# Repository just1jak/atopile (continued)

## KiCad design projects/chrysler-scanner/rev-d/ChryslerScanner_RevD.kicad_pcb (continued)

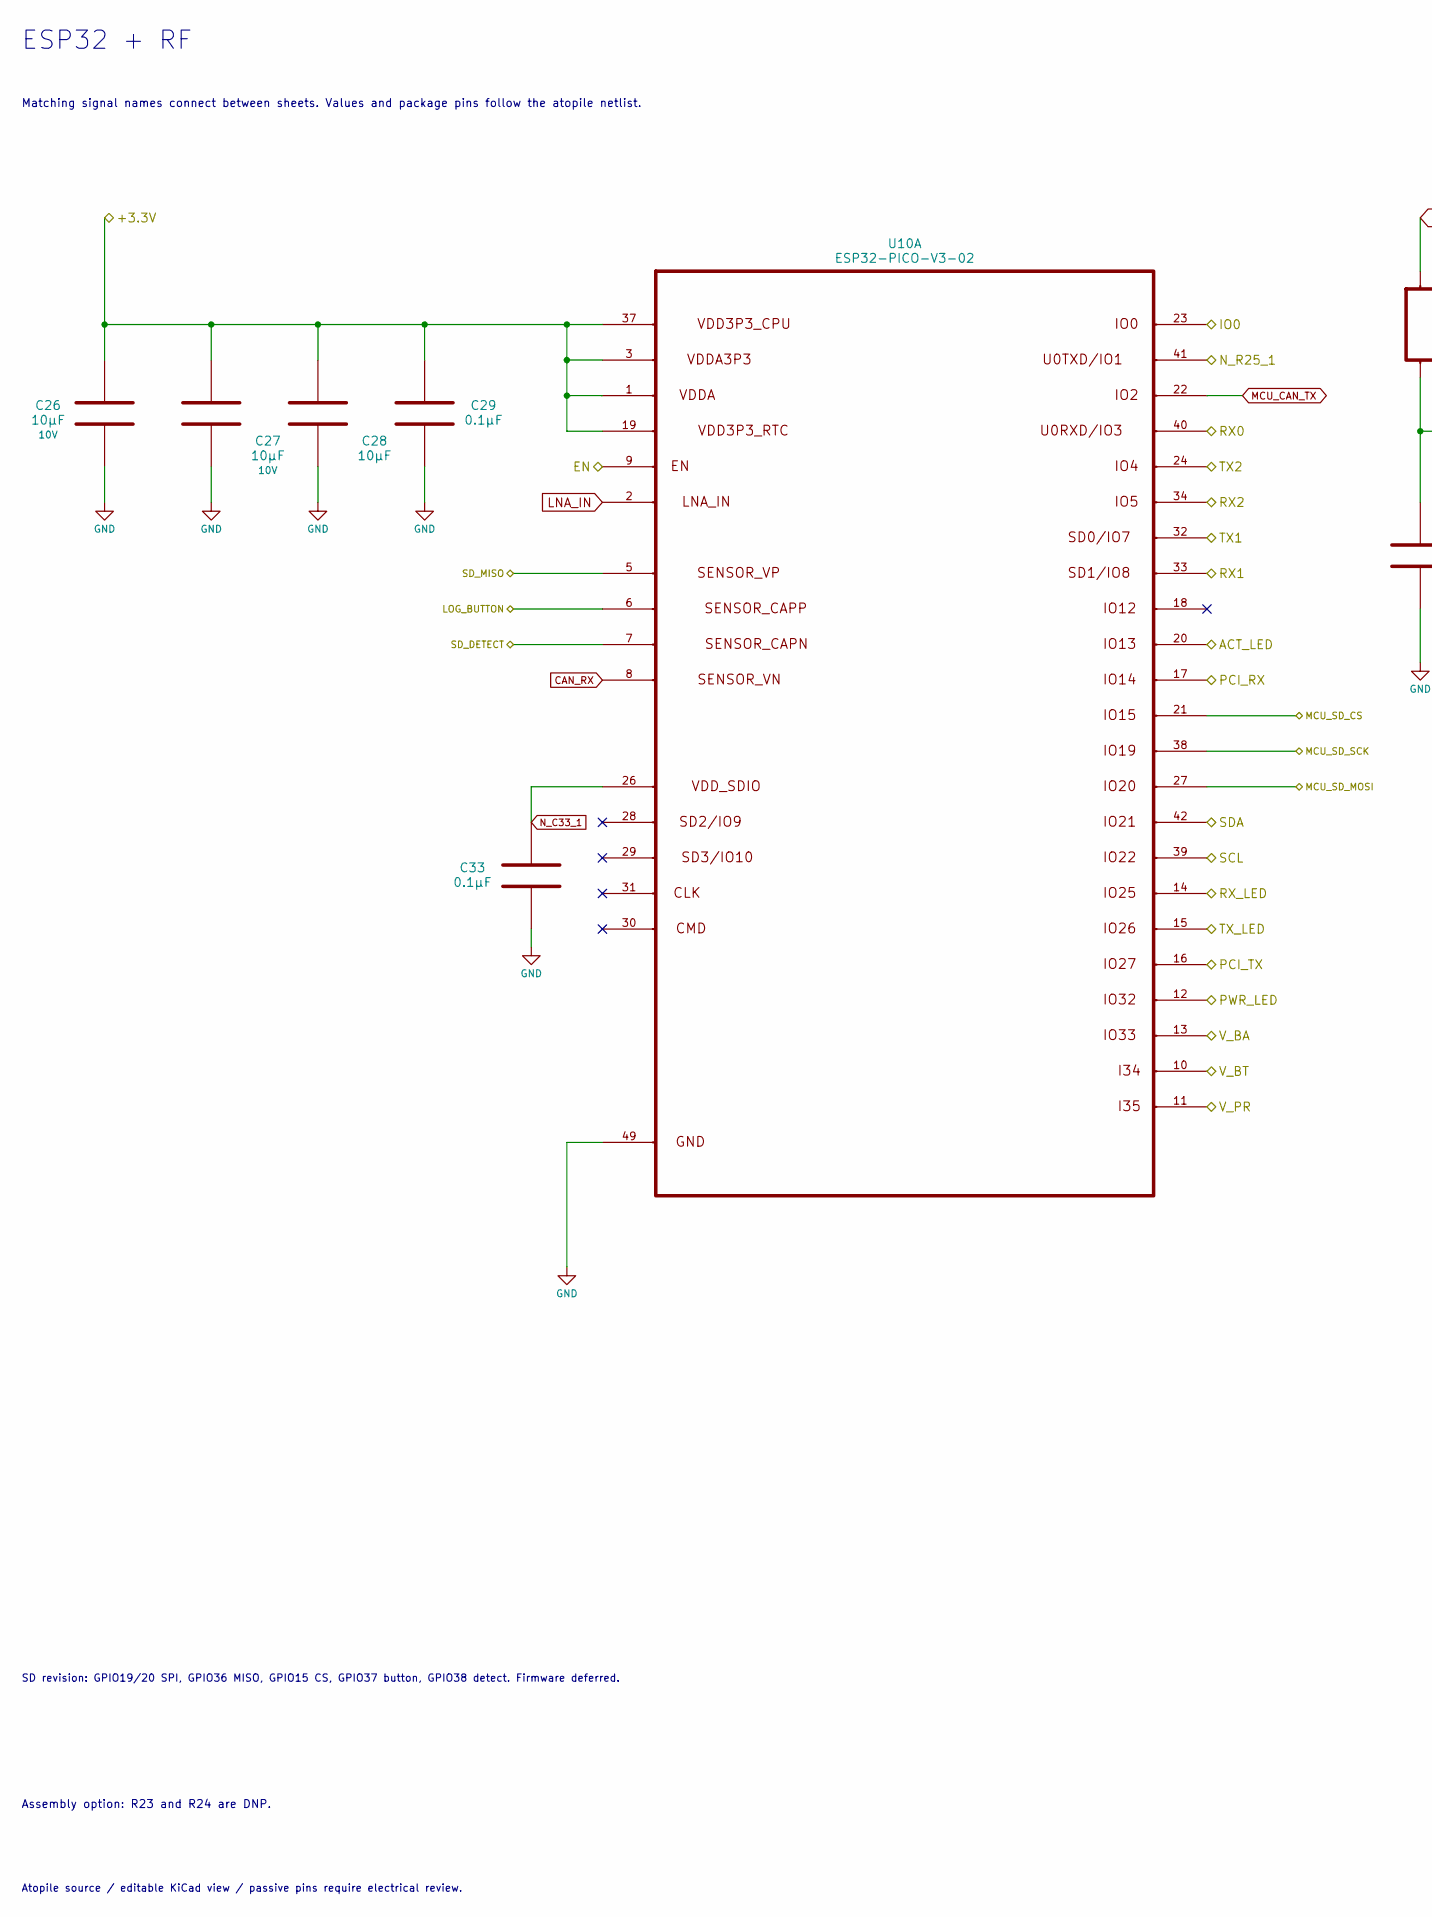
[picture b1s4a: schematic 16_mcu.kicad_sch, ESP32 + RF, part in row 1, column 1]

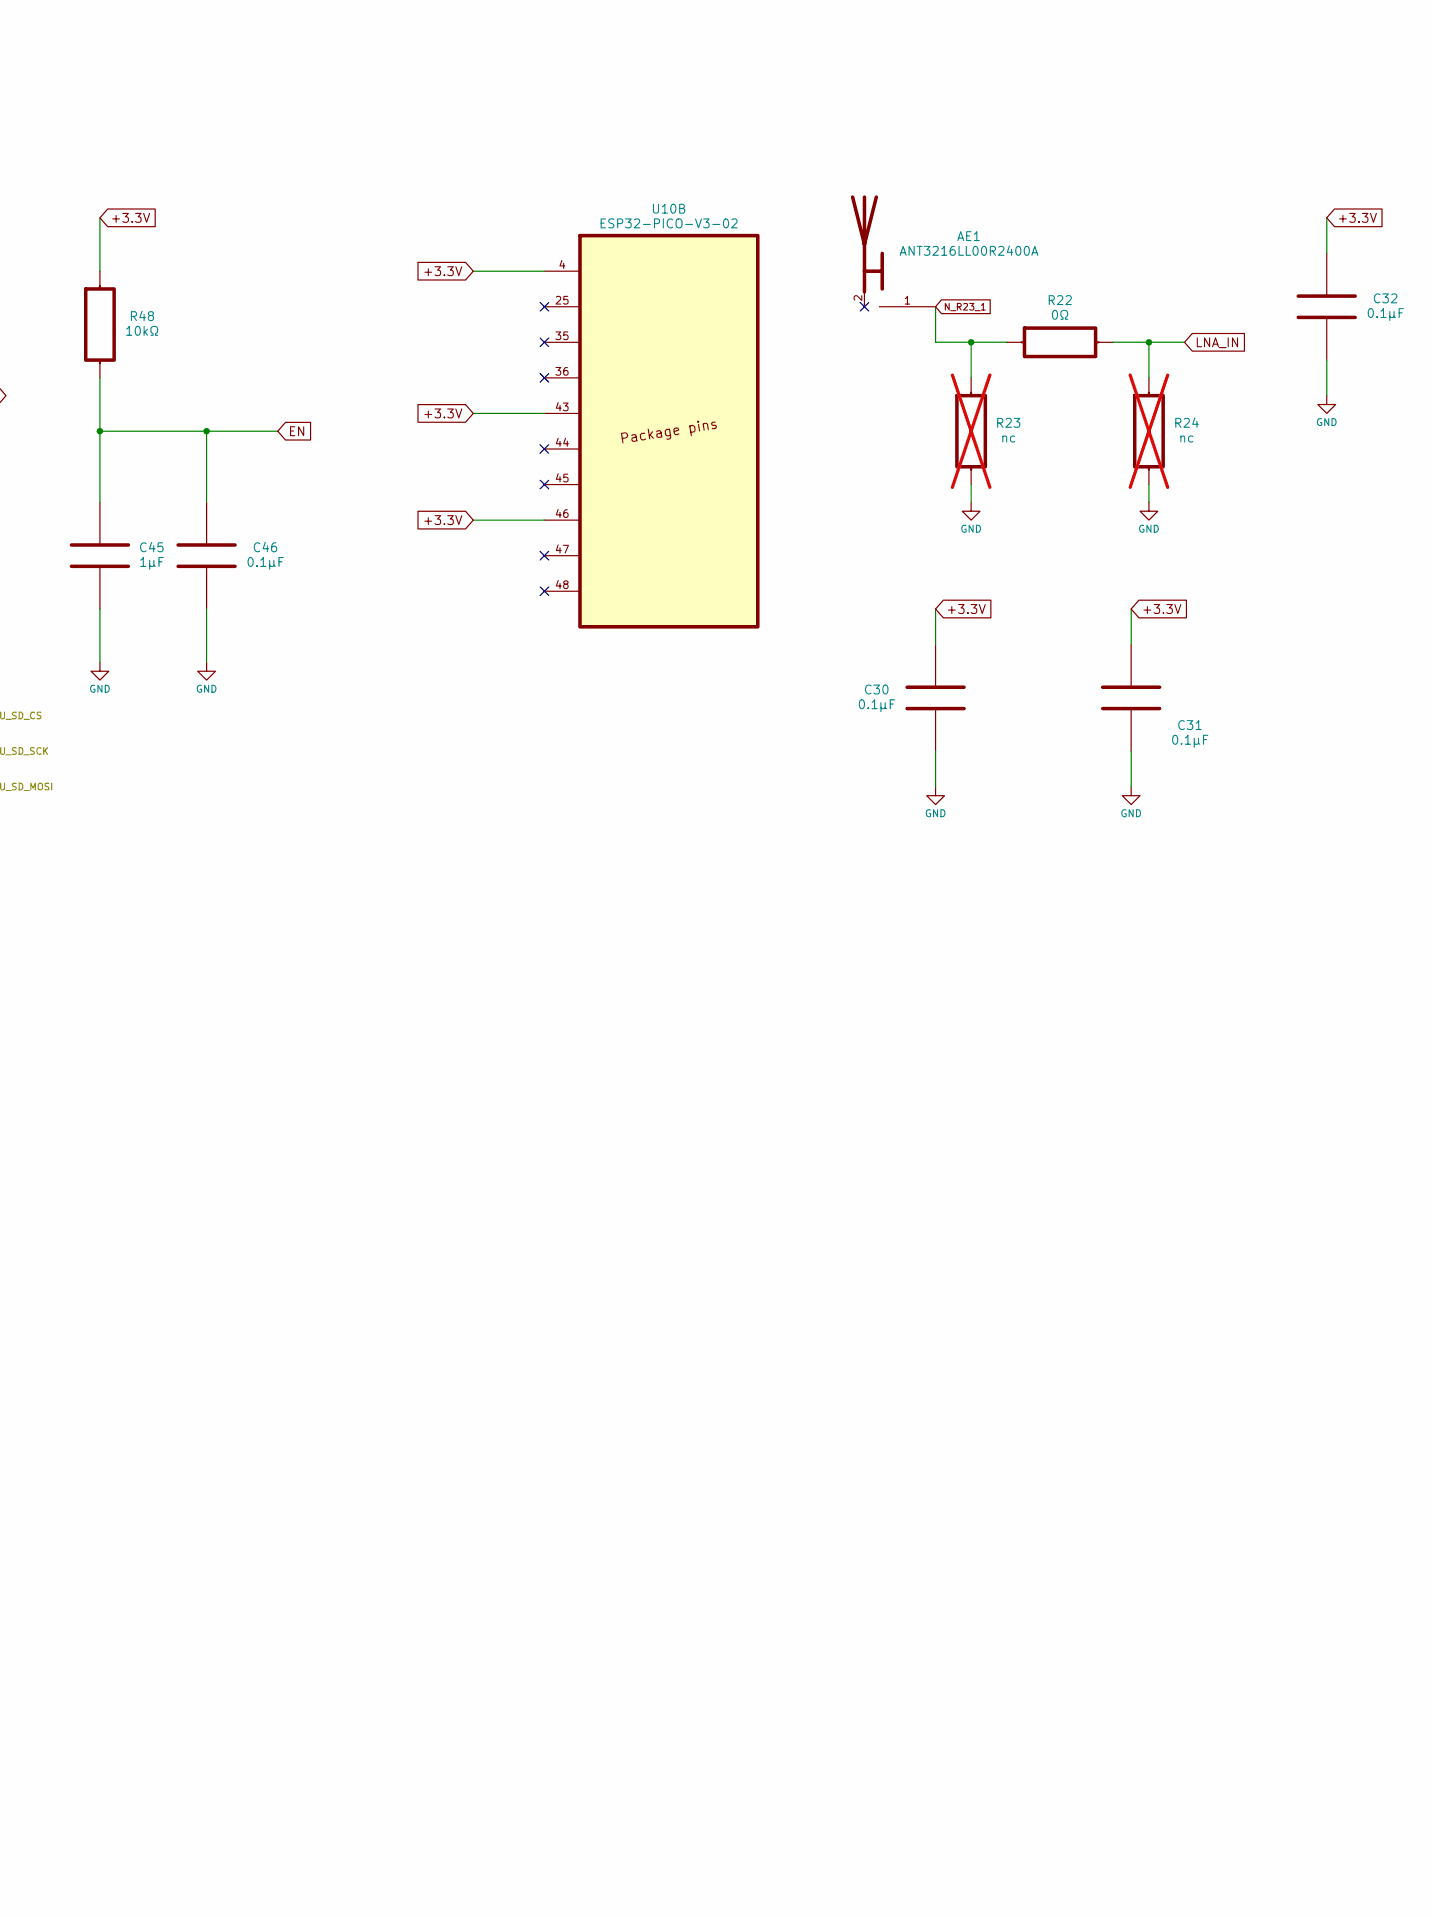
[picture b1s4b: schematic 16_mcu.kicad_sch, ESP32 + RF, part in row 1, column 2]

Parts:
AE1: ANT3216LL00R2400A; MPN ANT3216LL00R2400A
C26, C27: 10μF; C_0603_1608Metric; Voltage Rating 10V; Selected Voltage Rating 10V; MPN C1608X5R1A106K080AC
C28: 10μF; C_0603_1608Metric; Selected Voltage Rating 10V; Tolerance 10%; MPN C1608X5R1A106K080AC
C29, C30, C31, C32, C33, C46: 0.1μF; C_0603_1608Metric; Selected Voltage Rating 50V; Tolerance 10%; MPN C0603C104K5RACTU
C45: 1μF; C_0603_1608Metric; Selected Voltage Rating 16V; Tolerance 10%; MPN C0603C105K4RACTU
R22: 0Ω; R_0603_1608Metric; Tolerance jumper; MPN CRCW06030000Z0EA
R23, R24: nc; R_0603_1608Metric; MPN DNP_RF_TUNING; not fitted
R48: 10kΩ; R_0603_1608Metric; Tolerance 1%; MPN CRCW060310K0FKEA
U10: ESP32-PICO-V3-02; ESP32_PICO_V3_02; MPN ESP32-PICO-V3-02

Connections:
+3.3V: C26.1, C27.1, C28.1, C29.1, C30.1, C31.1, C32.1, R48.1, U10.1, U10.3, U10.4, U10.19, U10.37, U10.43, U10.46; also elsewhere on the board
ACT_LED: U10.20; also elsewhere on the board
CAN_RX: U10.8; also elsewhere on the board
EN: C45.1, C46.1, R48.2, U10.9; also elsewhere on the board
GND: C26.2, C27.2, C28.2, C29.2, C30.2, C31.2, C32.2, C33.2, C45.2, C46.2, R23.2, R24.2, U10.49; also elsewhere on the board
IO0: U10.23; also elsewhere on the board
LNA_IN: R22.2, R24.1, U10.2
LOG_BUTTON: U10.6; also elsewhere on the board
MCU_CAN_TX: U10.22; also elsewhere on the board
MCU_SD_CS: U10.21; also elsewhere on the board
MCU_SD_MOSI: U10.27; also elsewhere on the board
MCU_SD_SCK: U10.38; also elsewhere on the board
N_C33_1: C33.1, U10.26
N_R23_1: AE1.1, R22.1, R23.1
N_R25_1: U10.41; also elsewhere on the board
PCI_RX: U10.17; also elsewhere on the board
PCI_TX: U10.16; also elsewhere on the board
PWR_LED: U10.12; also elsewhere on the board
RX0: U10.40; also elsewhere on the board
RX1: U10.33; also elsewhere on the board
RX2: U10.34; also elsewhere on the board
RX_LED: U10.14; also elsewhere on the board
SCL: U10.39; also elsewhere on the board
SDA: U10.42; also elsewhere on the board
SD_DETECT: U10.7; also elsewhere on the board
SD_MISO: U10.5; also elsewhere on the board
TX1: U10.32; also elsewhere on the board
TX2: U10.24; also elsewhere on the board
TX_LED: U10.15; also elsewhere on the board
V_BA: U10.13; also elsewhere on the board
V_BT: U10.10; also elsewhere on the board
V_PR: U10.11; also elsewhere on the board

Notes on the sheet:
Atopile source / editable KiCad view / passive pins require electrical review.
Assembly option: R23 and R24 are DNP.
SD revision: GPIO19/20 SPI, GPIO36 MISO, GPIO15 CS, GPIO37 button, GPIO38 detect. Firmware deferred.
Matching signal names connect between sheets. Values and package pins follow the atopile netlist.
ESP32 + RF

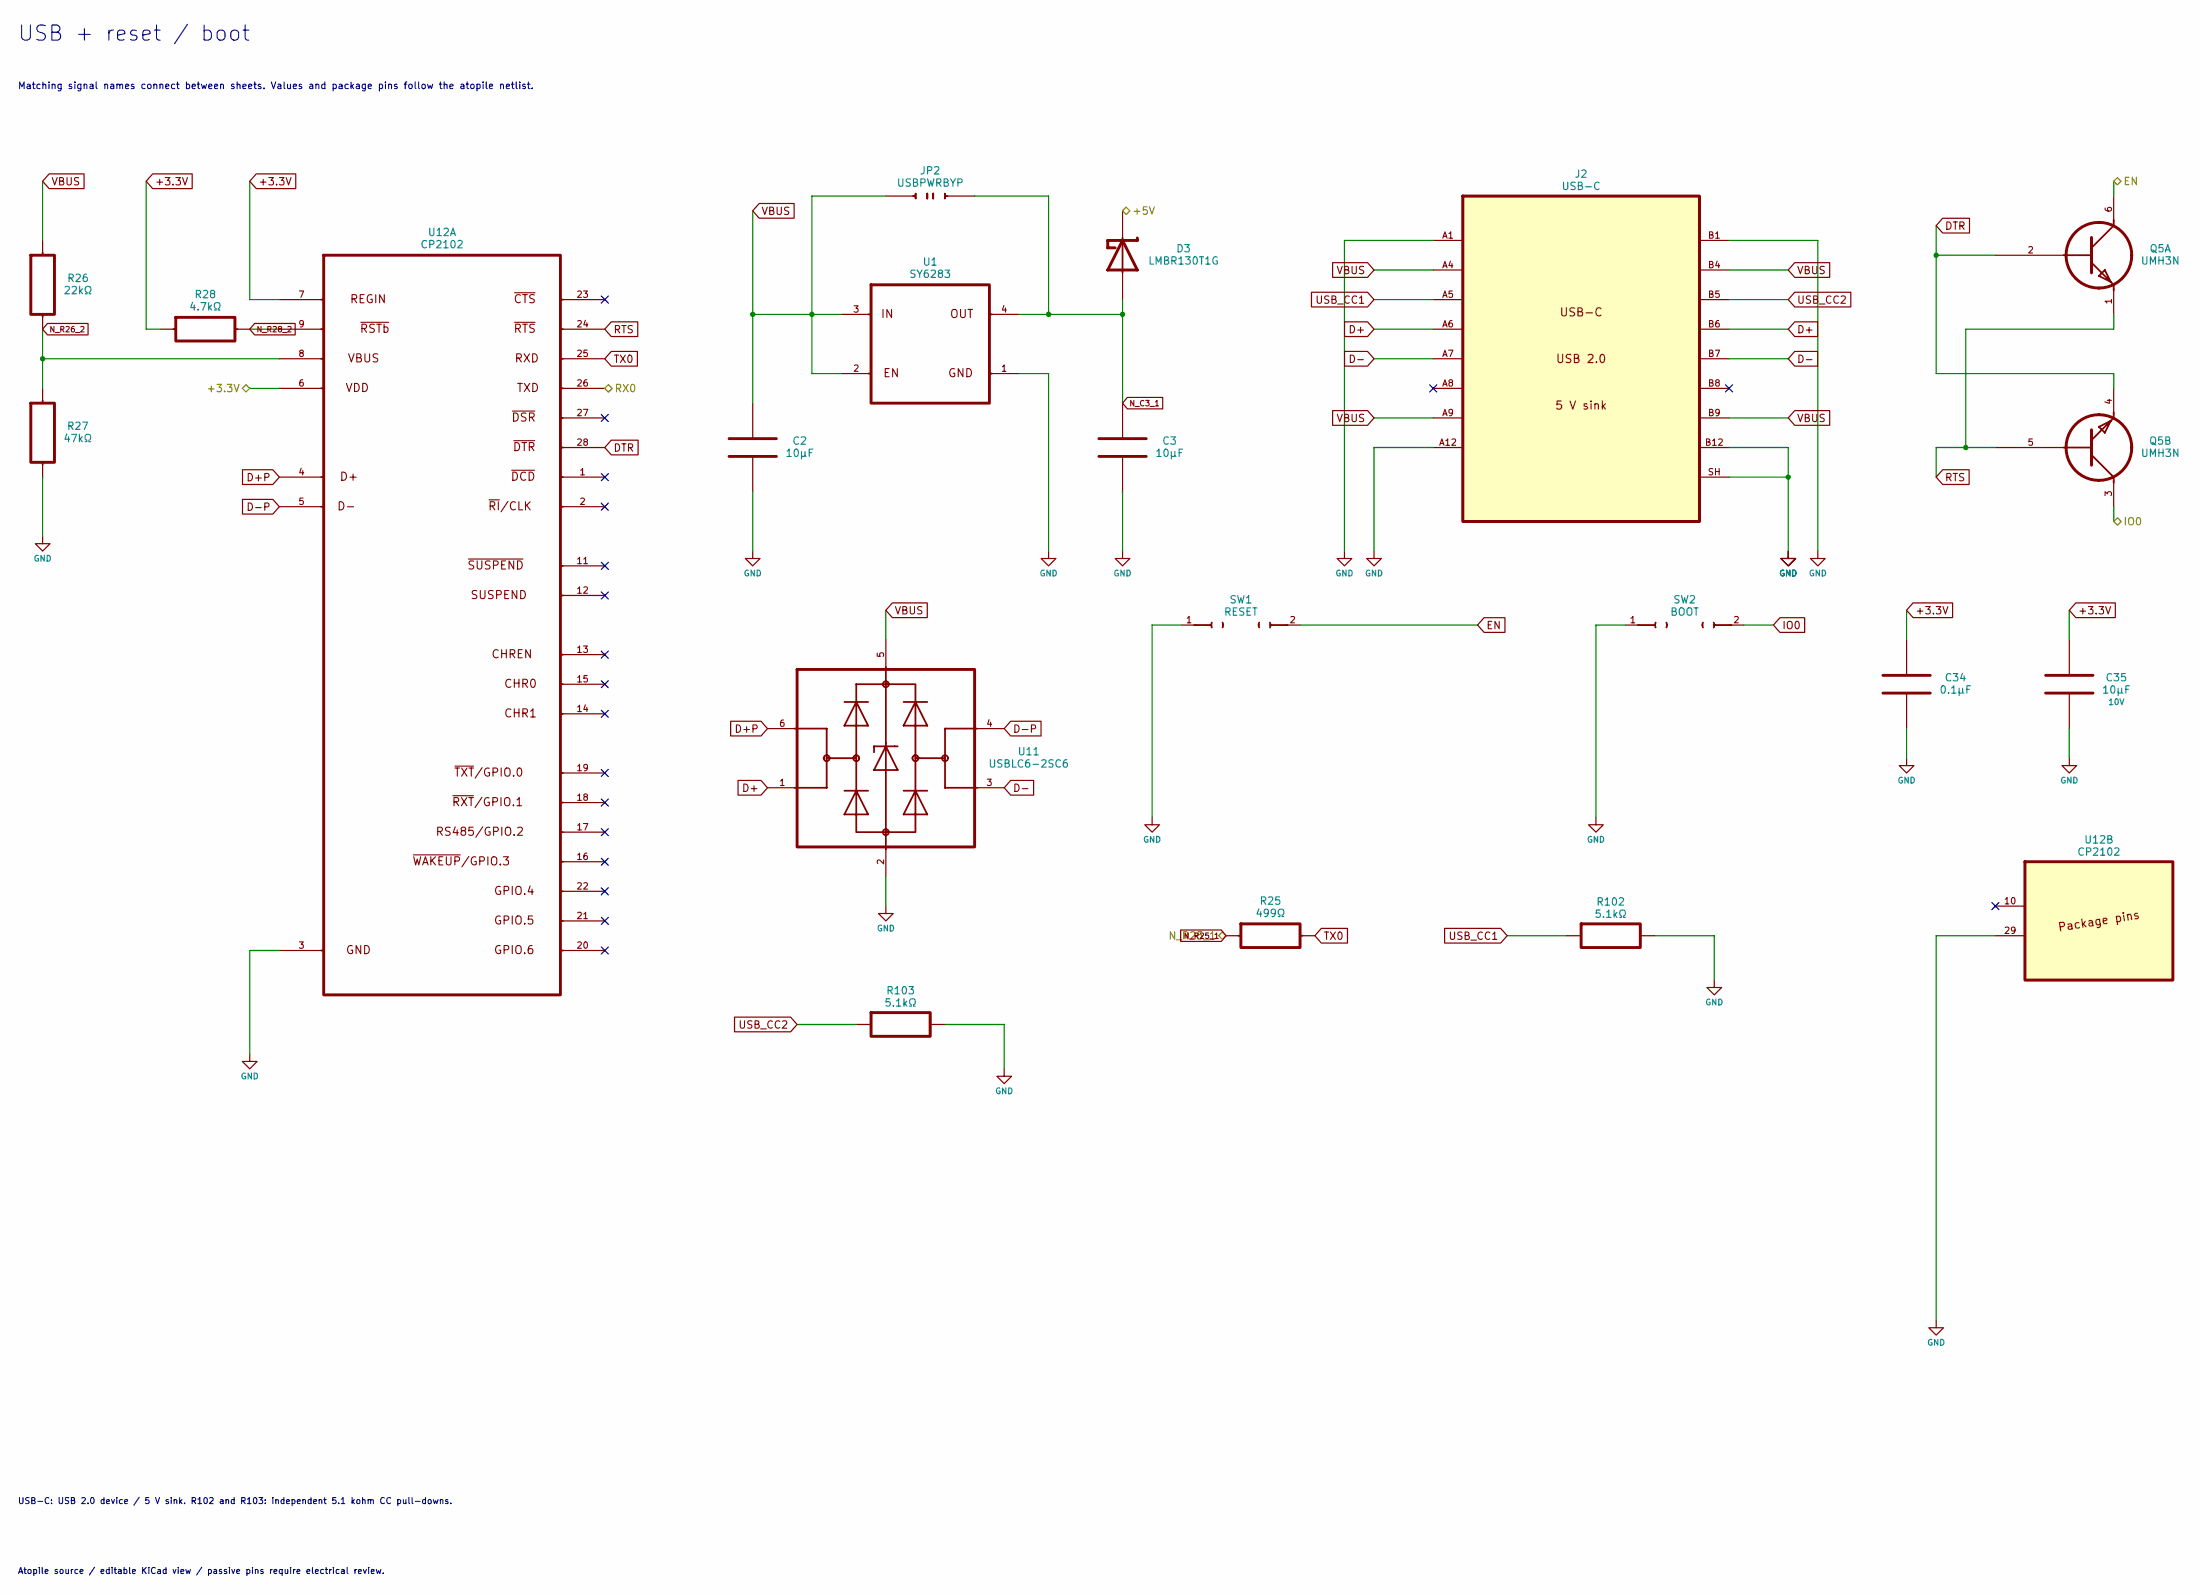
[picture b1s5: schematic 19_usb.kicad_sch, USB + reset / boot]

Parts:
C2, C3: 10μF; C_1206_3216Metric; Selected Voltage Rating 50V; Tolerance 10%; MPN CGA5L1X7R1H106K160AC
C34: 0.1μF; C_0603_1608Metric; Selected Voltage Rating 50V; Tolerance 10%; MPN C0603C104K5RACTU
C35: 10μF; C_0603_1608Metric; Voltage Rating 10V; Selected Voltage Rating 10V; MPN C1608X5R1A106K080AC
D3: LMBR130T1G; D_SOD-123; MPN LMBR130T1G
J2: USB-C; USB_C_Receptacle_GCT_USB4105-xx-A_16P_TopMnt_Horizontal; MPN USB4105-GF-A
JP2: USBPWRBYP; SolderJumper-2_P1.3mm_Open_Pad1.0x1.5mm; MPN SOLDER_BRIDGE_NO_COMPONENT
Q5: UMH3N; SOT-363_SC-70-6; MPN UMH3NTR
R25: 499Ω; R_0603_1608Metric; Tolerance 1%; MPN CRCW0603499RFKEA
R26: 22kΩ; R_0603_1608Metric; Tolerance 1%; MPN CRCW060322K0FKEA
R27: 47kΩ; R_0603_1608Metric; Tolerance 1%; MPN CRCW060347K0FKEA
R28: 4.7kΩ; R_0603_1608Metric; Tolerance 1%; MPN CRCW06034K70FKEA
R102, R103: 5.1kΩ; R_0603_1608Metric; Tolerance 1%; MPN CRCW06035K10FKEA
SW1: RESET; SW_SPST_TL3305A; MPN TL3305AF160QG
SW2: BOOT; SW_SPST_TL3305A; MPN TL3305AF160QG
U1: SY6283; SY6283_DFN4; MPN SY6283DRC
U11: USBLC6-2SC6; USBLC6_V140_Reference; MPN USBLC6-2SC6
U12: CP2102; CP2102_V140_Reference; MPN CP2102-GMR

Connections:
+3.3V: C34.1, C35.1, R28.1, U12.6, U12.7; also elsewhere on the board
+5V: D3.1; also elsewhere on the board
D+: J2.A6, J2.B6, U11.1
D+P: U11.6, U12.4
D-: J2.A7, J2.B7, U11.3
D-P: U11.4, U12.5
DTR: Q5.2, Q5.4, U12.28
EN: Q5.6, SW1.2; also elsewhere on the board
GND: C2.2, C3.2, C34.2, C35.2, J2.A1, J2.A12, J2.B1, J2.B12, J2.SH, R27.2, R102.2, R103.2, SW1.1, SW2.1, U1.1, U11.2, U12.3, U12.29; also elsewhere on the board
IO0: Q5.3, SW2.2; also elsewhere on the board
N_C3_1: C3.1, D3.2, JP2.2, U1.4
N_R25_1: R25.1; also elsewhere on the board
N_R26_2: R26.2, R27.1, U12.8
N_R28_2: R28.2, U12.9
RTS: Q5.1, Q5.5, U12.24
RX0: U12.26; also elsewhere on the board
TX0: R25.2, U12.25; also elsewhere on the board
USB_CC1: J2.A5, R102.1
USB_CC2: J2.B5, R103.1
VBUS: C2.1, J2.A4, J2.A9, J2.B4, J2.B9, JP2.1, R26.1, U1.2, U1.3, U11.5; also elsewhere on the board

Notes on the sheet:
USB + reset / boot
USB-C: USB 2.0 device / 5 V sink. R102 and R103: independent 5.1 kohm CC pull-downs.
Atopile source / editable KiCad view / passive pins require electrical review.
Matching signal names connect between sheets. Values and package pins follow the atopile netlist.

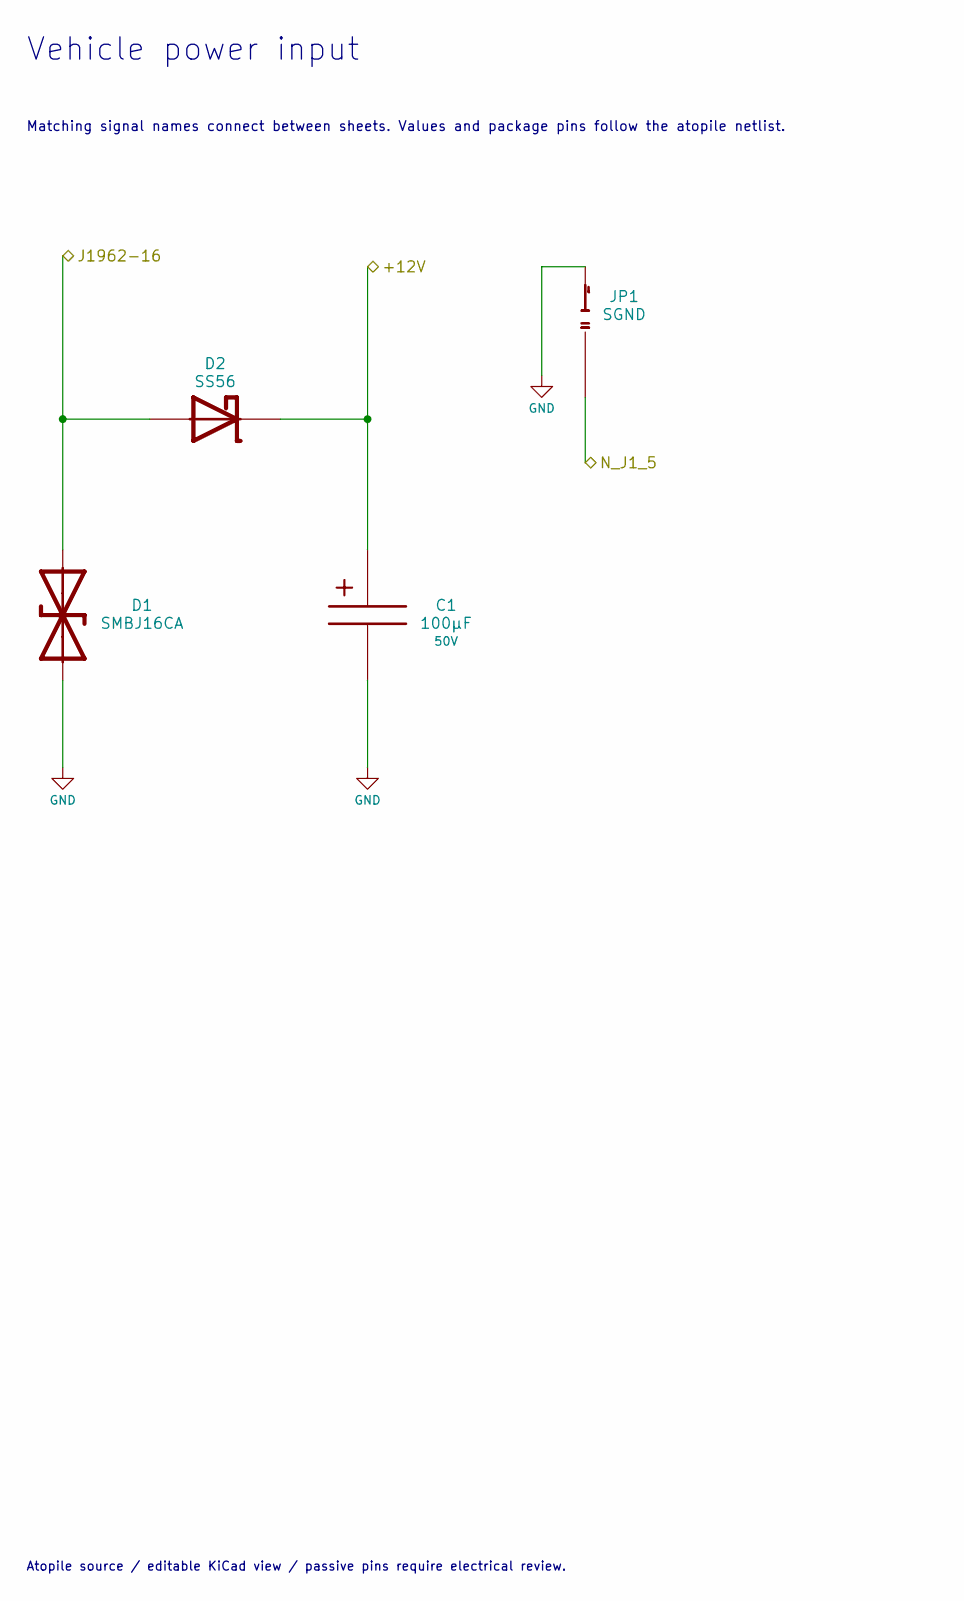
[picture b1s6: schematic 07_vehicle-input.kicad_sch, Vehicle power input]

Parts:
C1: 100μF; CP_Radial_D8.0mm_P3.50mm; Voltage Rating 50V; Selected Voltage Rating 50V; MPN UPW1H101MPD
D1: SMBJ16CA; D_SMB; MPN SMBJ16CA
D2: SS56; D_SMB; MPN SS56-E3/57T
JP1: SGND; SolderJumper-2_P1.3mm_Bridged_Pad1.0x1.5mm; MPN SOLDER_BRIDGE_NO_COMPONENT

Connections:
+12V: C1.1, D2.1; also elsewhere on the board
GND: C1.2, D1.2, JP1.2; also elsewhere on the board
J1962-16: D1.1, D2.2; also elsewhere on the board
N_J1_5: JP1.1; also elsewhere on the board

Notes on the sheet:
Atopile source / editable KiCad view / passive pins require electrical review.
Vehicle power input
Matching signal names connect between sheets. Values and package pins follow the atopile netlist.

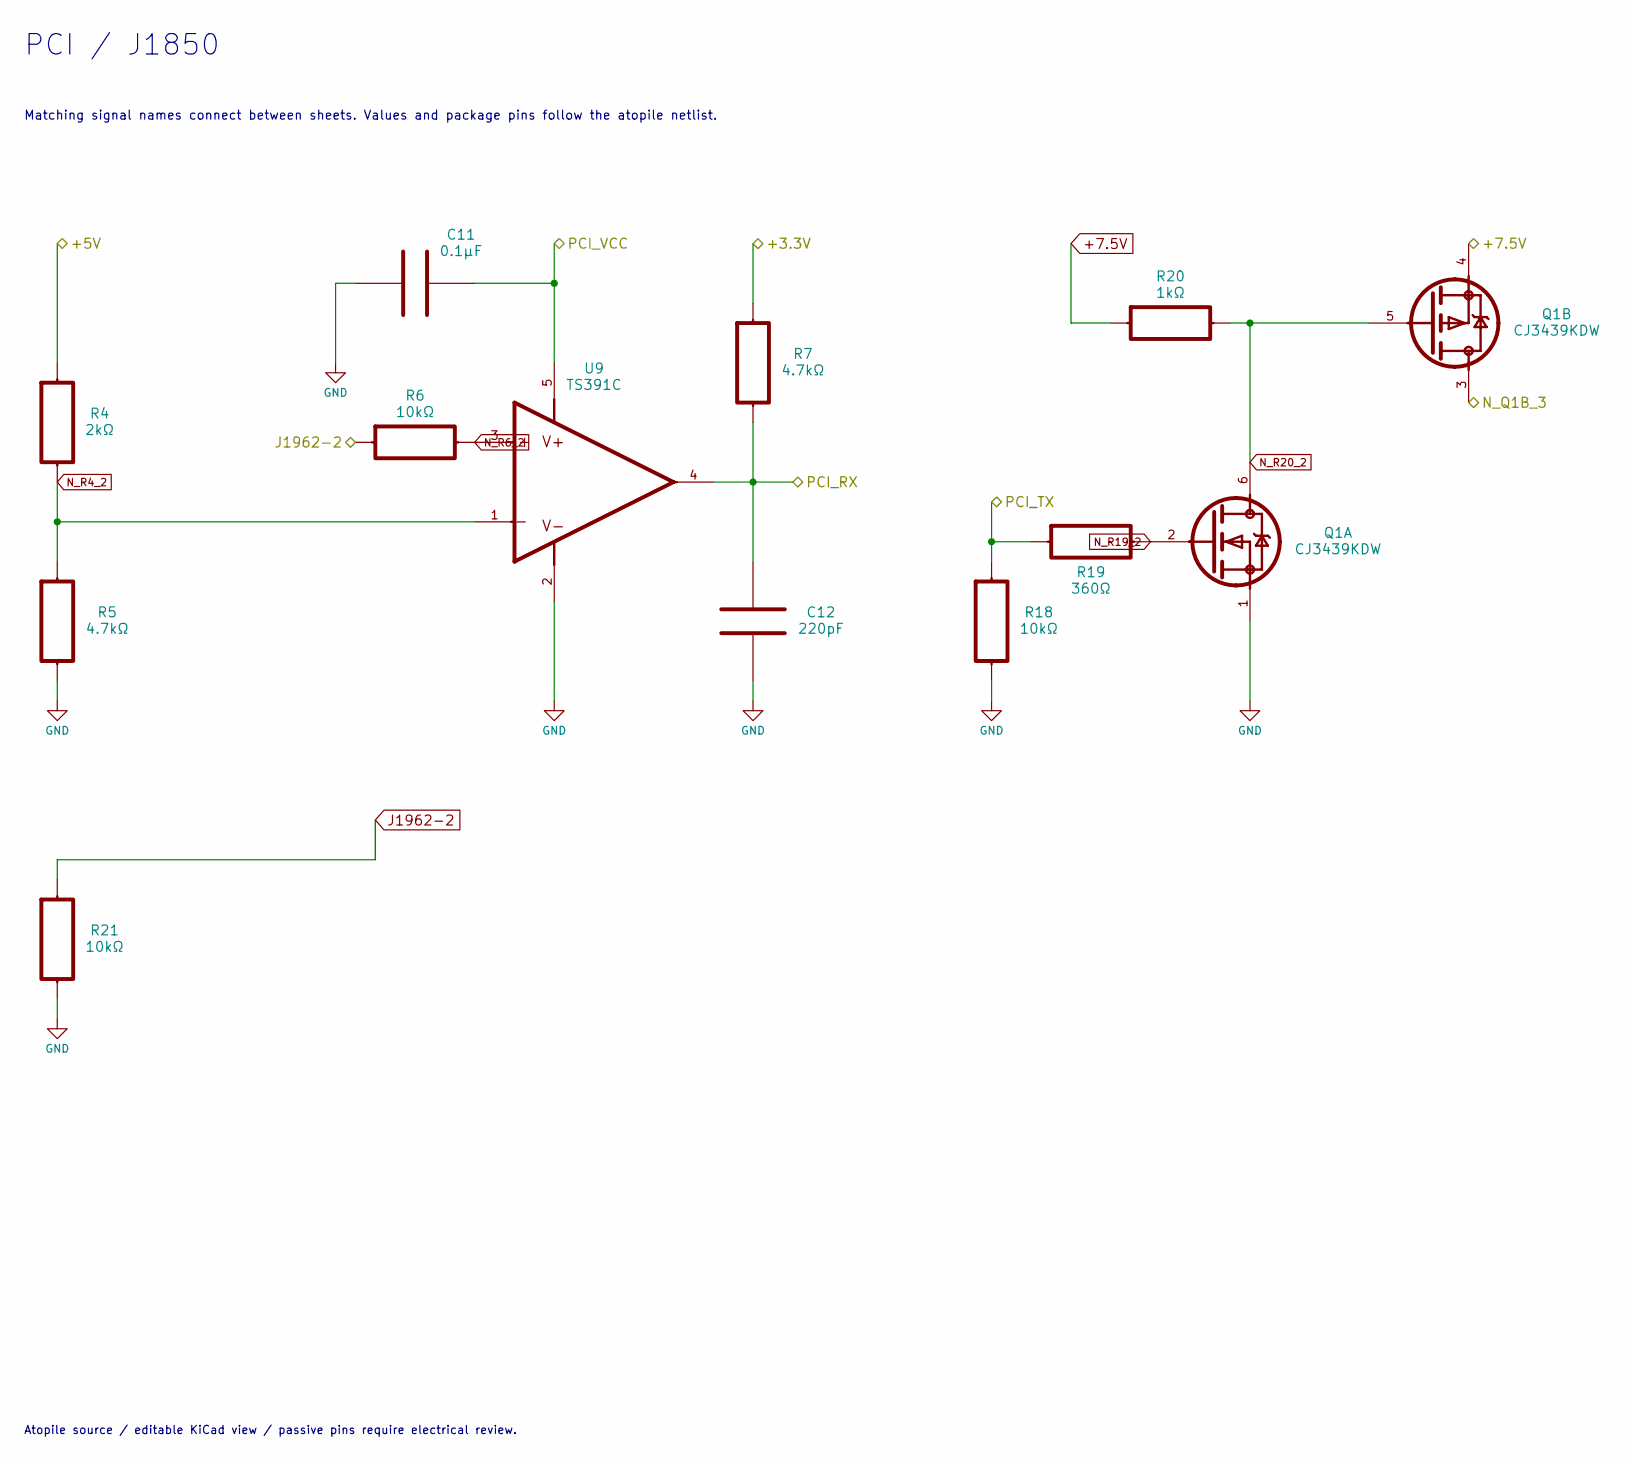
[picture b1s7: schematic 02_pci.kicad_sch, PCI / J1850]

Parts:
C11: 0.1μF; C_1206_3216Metric; Selected Voltage Rating 100V; Tolerance 10%; MPN C1206C104K1RACTU
C12: 220pF; C_1206_3216Metric; Selected Voltage Rating 100V; Tolerance 5%; MPN C1206C221J1GACTU
Q1: CJ3439KDW; SOT-363_SC-70-6_RR; MPN CJ3439KDW
R4: 2kΩ; R_0603_1608Metric; Tolerance 1%; MPN CRCW06032K00FKEA
R5, R7: 4.7kΩ; R_0603_1608Metric; Tolerance 1%; MPN CRCW06034K70FKEA
R6, R18, R21: 10kΩ; R_0603_1608Metric; Tolerance 1%; MPN CRCW060310K0FKEA
R19: 360Ω; R_1206_3216Metric; Tolerance 1%; MPN CRCW1206360RFKEA
R20: 1kΩ; R_1206_3216Metric; Tolerance 1%; MPN CRCW12061K00FKEA
U9: TS391C; SOT-23-5; MPN TS391ILT

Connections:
+3.3V: R7.1; also elsewhere on the board
+5V: R4.1; also elsewhere on the board
+7.5V: Q1.4, R20.1; also elsewhere on the board
GND: C11.1, C12.2, Q1.1, R5.2, R18.2, R21.2, U9.2; also elsewhere on the board
J1962-2: R6.1, R21.1; also elsewhere on the board
N_Q1B_3: Q1.3; also elsewhere on the board
N_R4_2: R4.2, R5.1, U9.1
N_R6_2: R6.2, U9.3
N_R19_2: Q1.2, R19.2
N_R20_2: Q1.5, Q1.6, R20.2
PCI_RX: C12.1, R7.2, U9.4; also elsewhere on the board
PCI_TX: R18.1, R19.1; also elsewhere on the board
PCI_VCC: C11.2, U9.5; also elsewhere on the board

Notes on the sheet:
Matching signal names connect between sheets. Values and package pins follow the atopile netlist.
PCI / J1850
Atopile source / editable KiCad view / passive pins require electrical review.

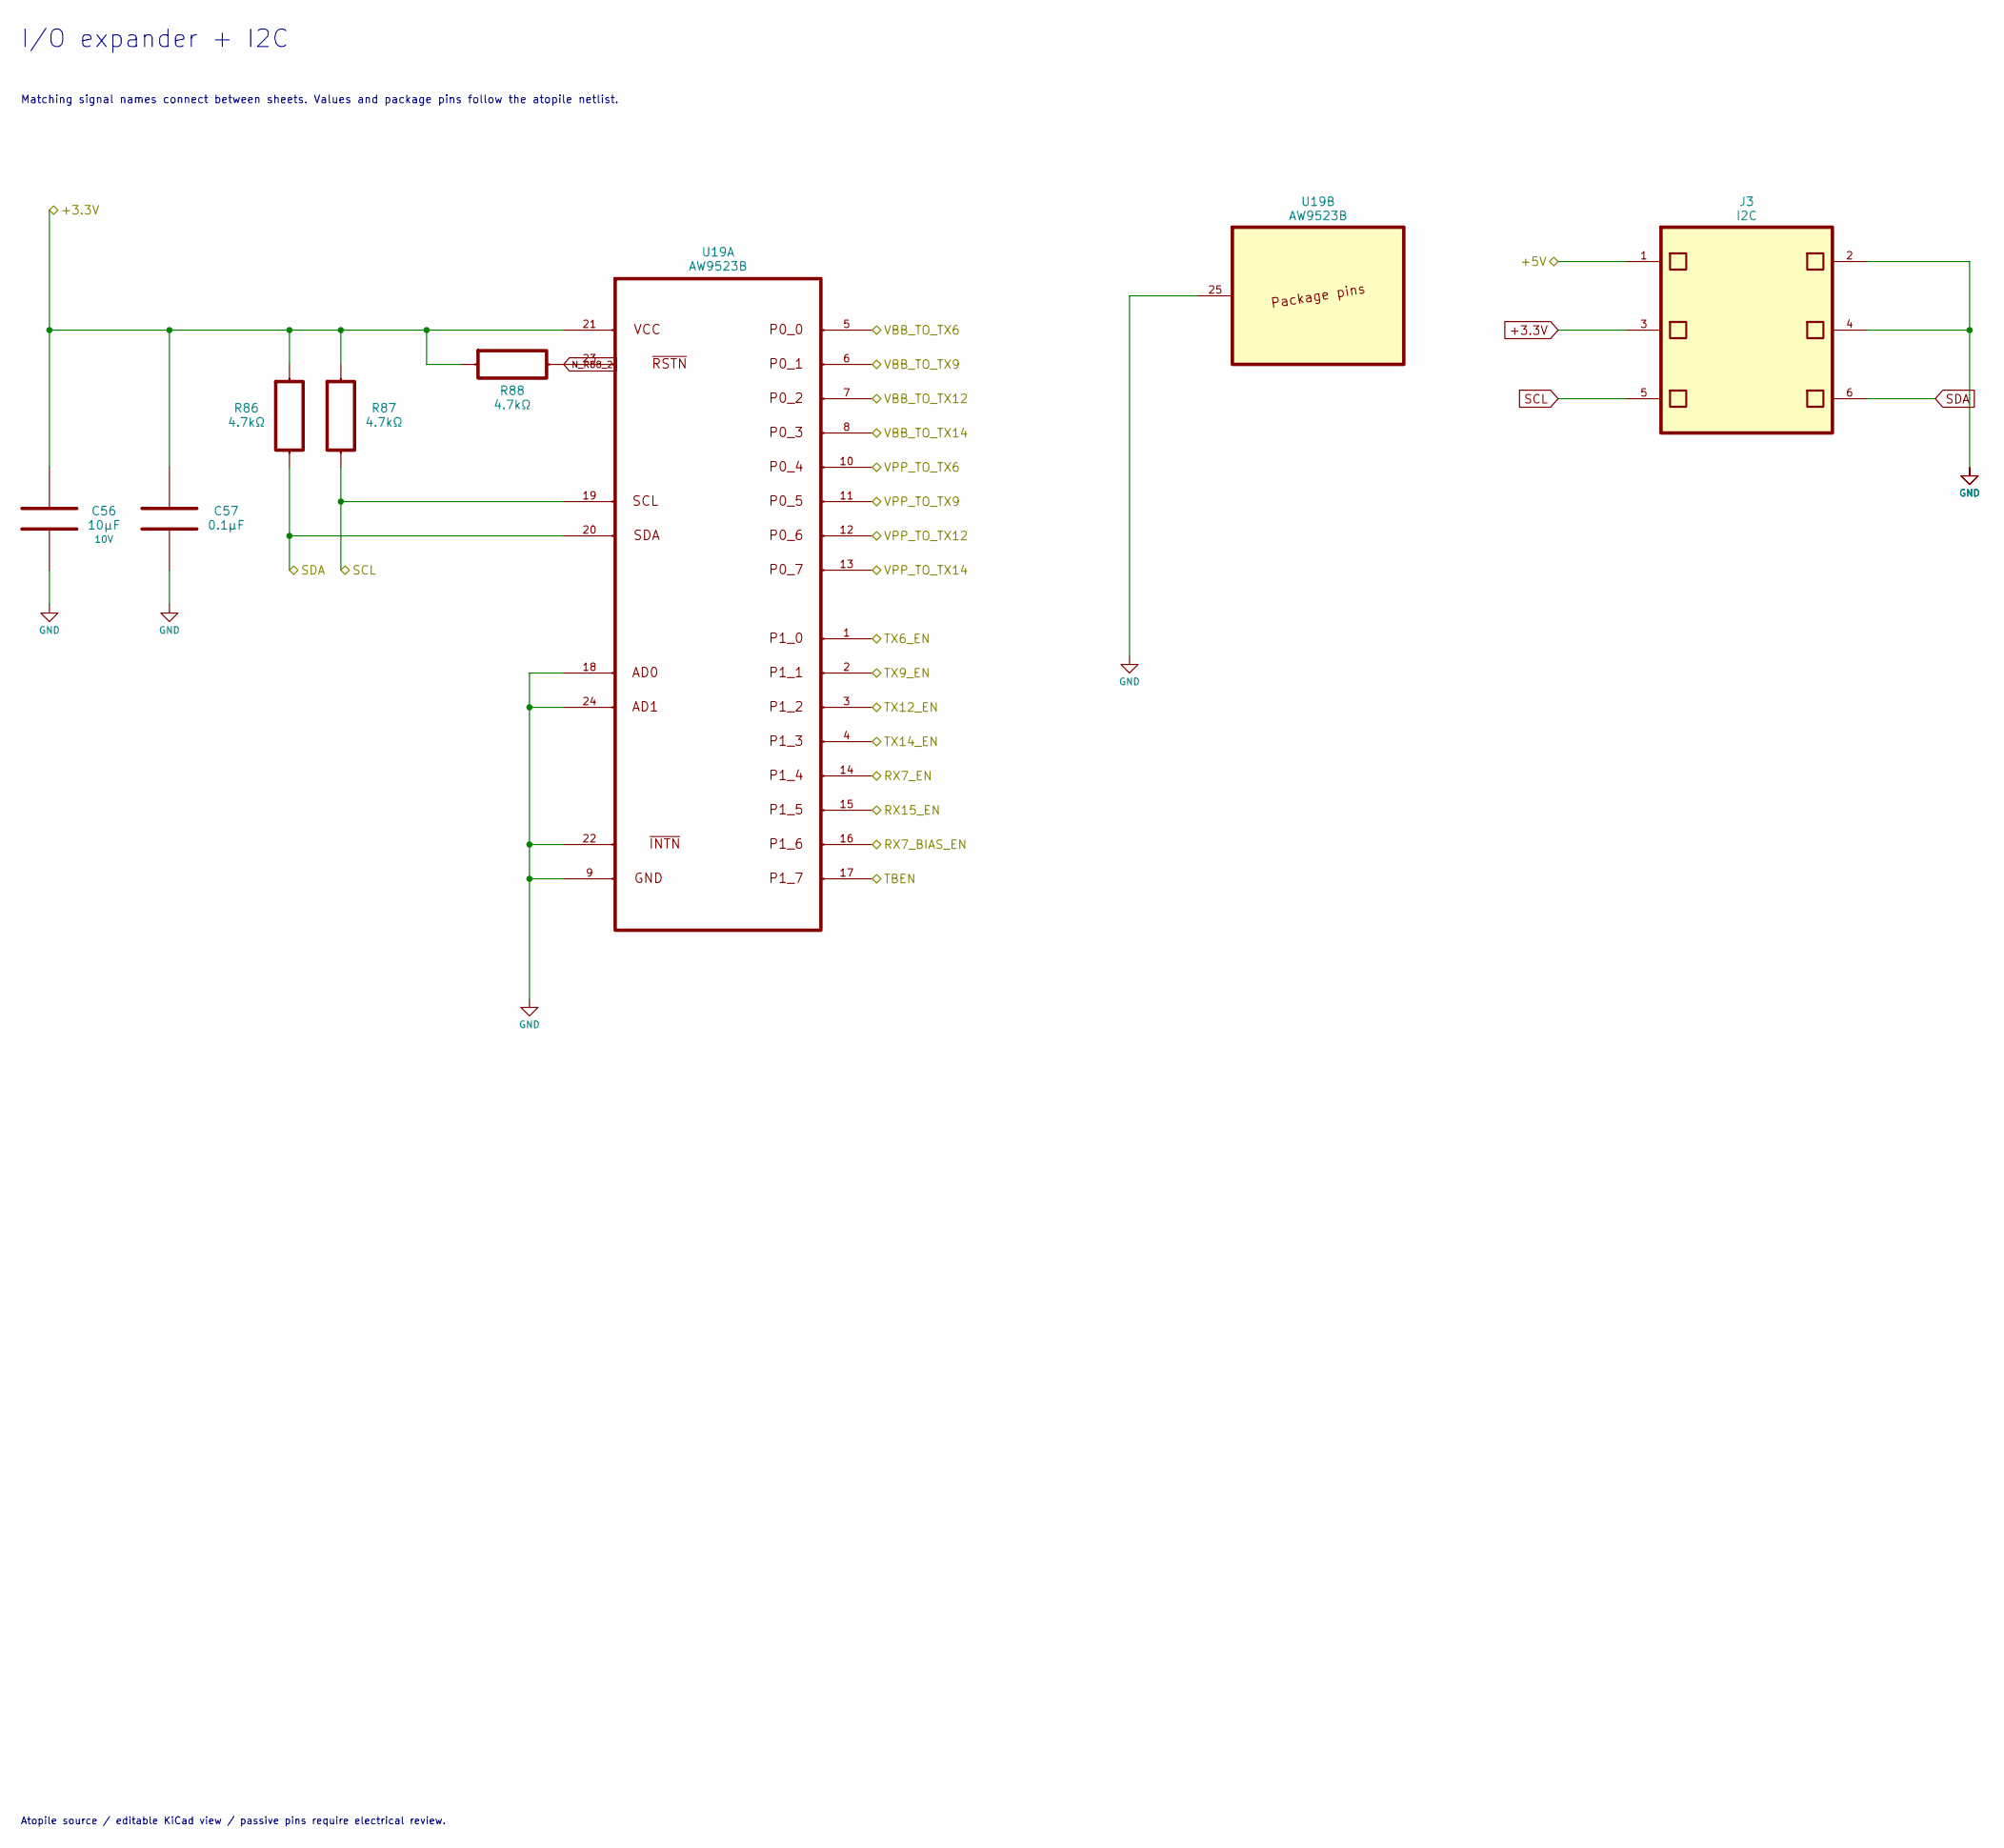
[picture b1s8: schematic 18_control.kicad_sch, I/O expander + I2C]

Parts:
C56: 10μF; C_0603_1608Metric; Voltage Rating 10V; Selected Voltage Rating 10V; MPN C1608X5R1A106K080AC
C57: 0.1μF; C_0603_1608Metric; Selected Voltage Rating 50V; Tolerance 10%; MPN C0603C104K5RACTU
J3: I2C; PinHeader_2x03_P2.54mm_Vertical; MPN TSW-103-07-G-D
R86, R87, R88: 4.7kΩ; R_0603_1608Metric; Tolerance 1%; MPN CRCW06034K70FKEA
U19: AW9523B; AW9523B_QFN24; MPN AW9523BTQR

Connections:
+3.3V: C56.1, C57.1, J3.3, R86.1, R87.1, R88.1, U19.21; also elsewhere on the board
+5V: J3.1; also elsewhere on the board
GND: C56.2, C57.2, J3.2, J3.4, U19.9, U19.18, U19.22, U19.24, U19.25; also elsewhere on the board
N_R88_2: R88.2, U19.23; also elsewhere on the board
RX7_BIAS_EN: U19.16; also elsewhere on the board
RX7_EN: U19.14; also elsewhere on the board
RX15_EN: U19.15; also elsewhere on the board
SCL: J3.5, R87.2, U19.19; also elsewhere on the board
SDA: J3.6, R86.2, U19.20; also elsewhere on the board
TBEN: U19.17; also elsewhere on the board
TX6_EN: U19.1; also elsewhere on the board
TX9_EN: U19.2; also elsewhere on the board
TX12_EN: U19.3; also elsewhere on the board
TX14_EN: U19.4; also elsewhere on the board
VBB_TO_TX6: U19.5; also elsewhere on the board
VBB_TO_TX9: U19.6; also elsewhere on the board
VBB_TO_TX12: U19.7; also elsewhere on the board
VBB_TO_TX14: U19.8; also elsewhere on the board
VPP_TO_TX6: U19.10; also elsewhere on the board
VPP_TO_TX9: U19.11; also elsewhere on the board
VPP_TO_TX12: U19.12; also elsewhere on the board
VPP_TO_TX14: U19.13; also elsewhere on the board

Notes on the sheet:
I/O expander + I2C
Matching signal names connect between sheets. Values and package pins follow the atopile netlist.
Atopile source / editable KiCad view / passive pins require electrical review.
